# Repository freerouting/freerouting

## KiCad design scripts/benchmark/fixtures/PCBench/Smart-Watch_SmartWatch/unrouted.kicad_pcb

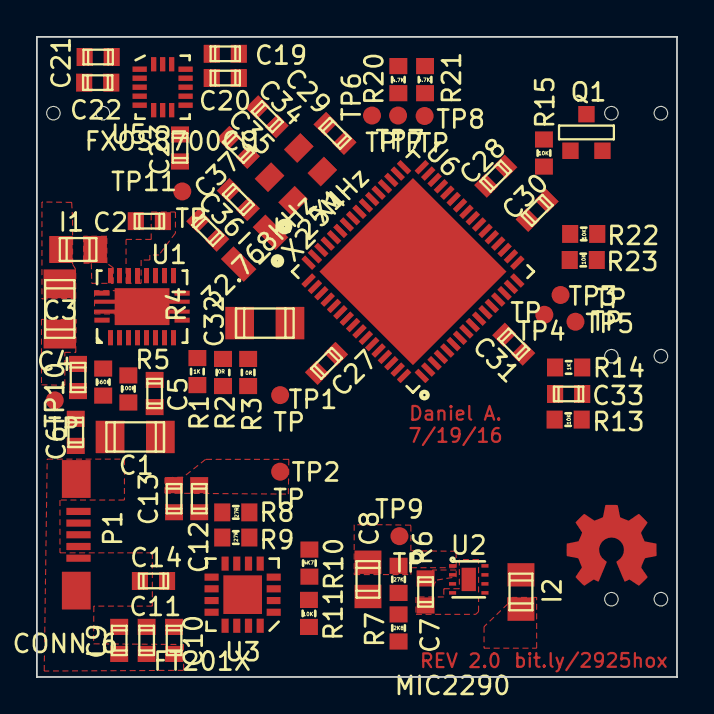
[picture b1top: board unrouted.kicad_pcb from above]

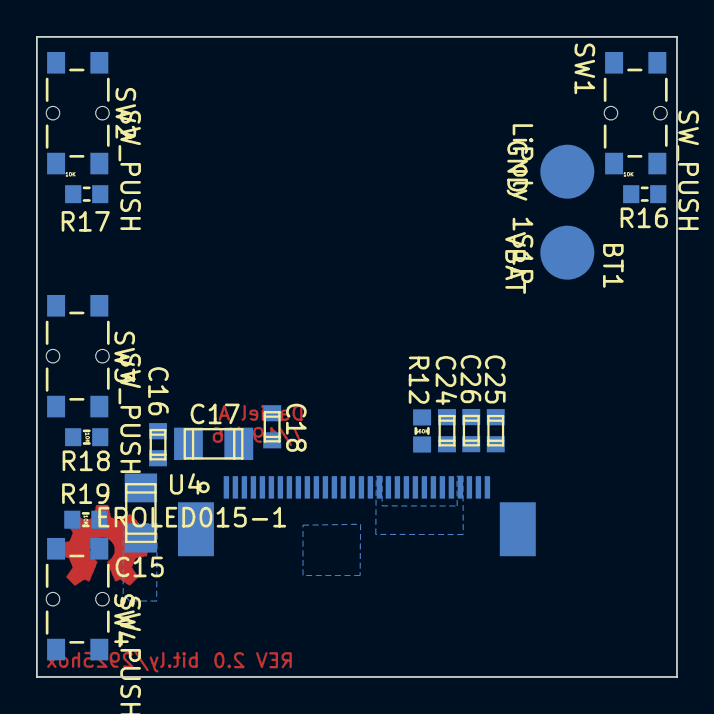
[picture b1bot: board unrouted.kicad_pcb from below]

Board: 4 copper layers, 35.6 x 35.6 mm, 88 parts (18 on the bottom side), 65 nets, no tracks yet.

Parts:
BT1: LiPoly 1S1P; CON_SM_3mm_2pin
C1, C3, C15, C32: 10u; c_1206
C2, C9, C19, C25: 4.7u; c_0603
C4: 27p; c_0603
C5: 180p; c_0603
C6, C10, C11, C14, C16, C20, C21, C22, C23, C26, C27, C28, C29, C30, C31, C33: 100n; c_0603
C7, C18, C24: 1u; c_0603
C8: 10u; c_0805
C12, C13: 47p; c_0603
C17: 4.7u; c_1206
C34, C35: 15p; c_0603
C36, C37: 9p1; c_0603
I1, I2: 10uH; r_0805
P1: CONN_6; USB-Micro-B
Q1: MMBT2222A; SOT23EBC
R1, R14: 1K; r_0603
R2, R3: 0R; r_0603
R4, R12: 560K; r_0603
R5: 100K; r_0603
R6: 27K; r_0603
R7: 2K8; r_0603
R8, R9: 27R; r_0603
R10: 4K7; r_0603
R11, R13, R15, R16, R17, R18, R19, R22, R23: 10K; r_0603
R20, R21: 4.7K; r_0603
SW1, SW2, SW3, SW4: SW_PUSH; 4.7x3.5mm_TCK_SW
TP1, TP2, TP3, TP4, TP5, TP6, TP7, TP8, TP9, TP10, TP11: TP; TP-1mm
U1: BQ25010; 20-VFQFN
U2: MIC2290; 8-VFDFN
U3: FT201X; QFN-16-ExPad
U4: EROLED015-1; ZIF_30pin_0.5pitch
U5: FXOS8700CQ; QFN-16
U6: PIC32MX370F512H; QFN-64
X1: 25MHz; ABM8
X2: 32.768KHz; Crystal_9HT10

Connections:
+3.3V: C3.1, C4.1, C7.1, C9.1, C10.1, C11.1, C18.1, C25.1, C26.1, C27.1, C28.1, C29.1, C30.1, C31.1, I1.2, I2.1, R4.2, R13.2, R20.1, R21.1, SW1.2, SW2.2, SW3.2, SW4.2, TP1.1, U2.2, U3.10, U4.4, U4.17, U4.18, U4.27, U6.10, U6.19, U6.26, U6.38, U6.57
+13V: C8.1, C15.1, C16.1, R6.1, TP9.1, U2.1, U4.2
/BAT/2: R22.2, R23.1, U6.17
/LCD/Sensors/CS: U4.19, U6.44
/LCD/Sensors/D0: U4.14, U6.60
/LCD/Sensors/D1: U4.13, U6.61
/LCD/Sensors/D2: U4.12, U6.62
/LCD/Sensors/D3: U4.11, U6.63
/LCD/Sensors/D4: U4.10, U6.64
/LCD/Sensors/D5: U4.9, U6.1
/LCD/Sensors/D6: U4.8, U6.2
/LCD/Sensors/D7: U4.7, U6.3
/LCD/Sensors/D/C: U4.20, U6.30
/LCD/Sensors/E: U4.15, U6.52
/LCD/Sensors/FX_RST: U5.16, U6.31
/LCD/Sensors/INT1: U5.11, U6.35
/LCD/Sensors/INT2: U5.9, U6.32
/LCD/Sensors/R/W: U4.16, U6.53
/LCD/Sensors/RES: U4.21, U6.43
/LCD/Sensors/SCL: R20.2, TP7.1, U3.16, U5.4, U6.37
/LCD/Sensors/SDA: R21.2, TP8.1, U3.2, U5.6, U6.36
/MOTOR: R15.2, U6.18
/RTCC: TP6.1, U6.42
/SW1: R16.2, SW1.1, U6.8
/SW2: R17.2, SW2.1, U6.6
/SW3: R18.2, SW3.1, U6.5
/SW4: R19.2, SW4.1, U6.4
/USB/Power/Boost-En: U2.3, U6.33
/USB/Power/CBUS2: U3.5, U6.24
/USB/Power/CBUS4: U3.4, U6.23
/USB/Power/D+: C13.1, P1.3, R9.1
/USB/Power/D-: C12.1, P1.2, R8.1
/USB/Power/FTDI_RST: U3.9, U6.29
/USB/Power/STAT1: U1.7, U6.59
/USB/Power/STAT2: U1.8, U6.58
/USB/Power/USB +5V: C1.1, C6.1, P1.1, R10.2, TP10.1, U1.6
/USB/Power/nPG: U1.14, U6.34
GND: BT1.2, C1.2, C2.2, C3.2, C5.2, C6.2, C7.2, C8.2, C9.2, C10.2, C11.2, C12.2, C13.2, C14.2, C15.2, C16.2, C17.2, C18.2, C19.2, C20.2, C21.2, C22.2, C23.2, C24.2, C25.2, C26.2, C27.2, C28.2, C29.2, C30.2, C31.2, C32.2, C33.2, C34.2, C35.2, C36.2, C37.2, P1.5, P1.6, Q1.1, R1.2, R2.2, R5.1, R7.2, R11.1, R12.1, R16.1, R17.1, R18.1, R19.1, R23.2, TP2.1, U1.3, U1.9, U1.15, U1.18, U1.20, U1.21, U2.4, U2.8, U2.9, U3.3, U3.13, U3.17, U4.1, U4.28, U4.30, U5.3, U5.5, U5.7, U5.10, U5.12, U5.13, U6.9, U6.20, U6.25, U6.41, U6.65, X1.3, X1.4
unnamed: C34.1, U6.39, X1.2
unnamed: C35.1, U6.40, X1.1
unnamed: TP3.1, U6.16
unnamed: TP4.1, U6.15
unnamed: C33.1, R13.1, R14.1
unnamed: C36.1, U6.48, X2.2
unnamed: C37.1, U6.47, X2.1
unnamed: Q1.2, R15.1
unnamed: R14.2, TP5.1, U6.7
unnamed: C32.1, U6.56
unnamed: I1.1, U1.19
unnamed: C4.2, C5.1, R4.1, R5.2, U1.2
unnamed: I2.2, U2.7
unnamed: R2.1, R3.2, U1.13
unnamed: R1.1, U1.12
unnamed: R10.1, R11.2, U3.15
unnamed: C14.1, U3.1, U3.8
unnamed: R9.2, U3.6
unnamed: R6.2, R7.1, U2.6
unnamed: R8.2, U3.7
unnamed: C19.1, C20.1, C21.1, U5.1, U5.14
unnamed: C22.1, U5.2
unnamed: C23.1, U5.8
unnamed: R12.2, U4.22
unnamed: C24.1, U4.26
unnamed: C17.1, U4.3
VBAT: BT1.1, C2.1, R3.1, R22.1, TP11.1, U1.4, U1.16, U1.17

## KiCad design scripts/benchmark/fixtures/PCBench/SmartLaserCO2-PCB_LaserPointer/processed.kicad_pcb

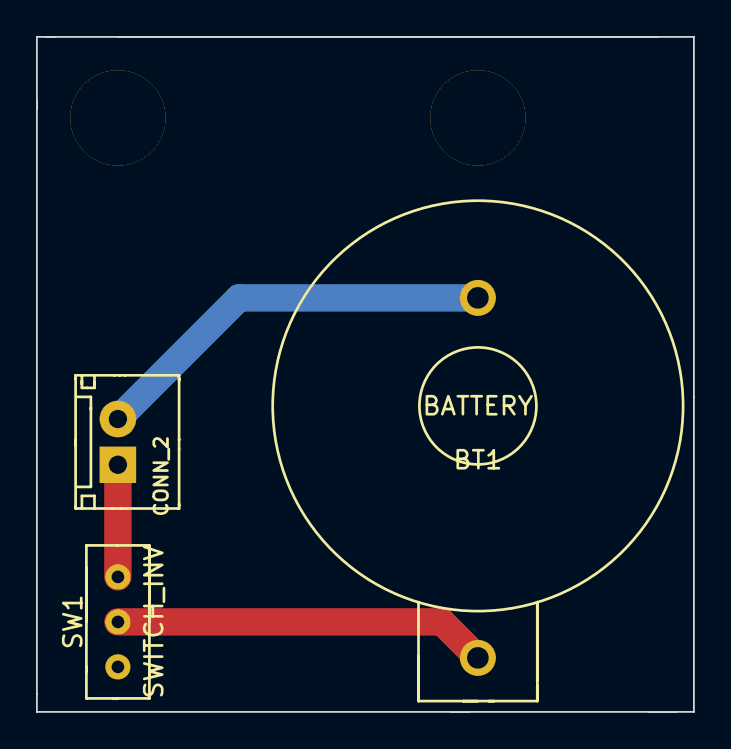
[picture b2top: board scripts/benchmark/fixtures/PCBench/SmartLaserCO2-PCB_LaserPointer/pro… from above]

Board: 2 copper layers, 36.5 x 37.5 mm, 5 parts (0 on the bottom side), 3 nets.

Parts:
BT1: BATTERY; CH25-2032LF
J1: CONN_2; PIN_ARRAY_2X1
Ref**: Val**; HOLE_M5
Ref**_2: Val**; HOLE_M5
SW1: SWITCH_INV; SS-12D00-G5

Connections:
GND: BT1.2, J1.2
unnamed: J1.1, SW1.1
unnamed: BT1.1, SW1.2

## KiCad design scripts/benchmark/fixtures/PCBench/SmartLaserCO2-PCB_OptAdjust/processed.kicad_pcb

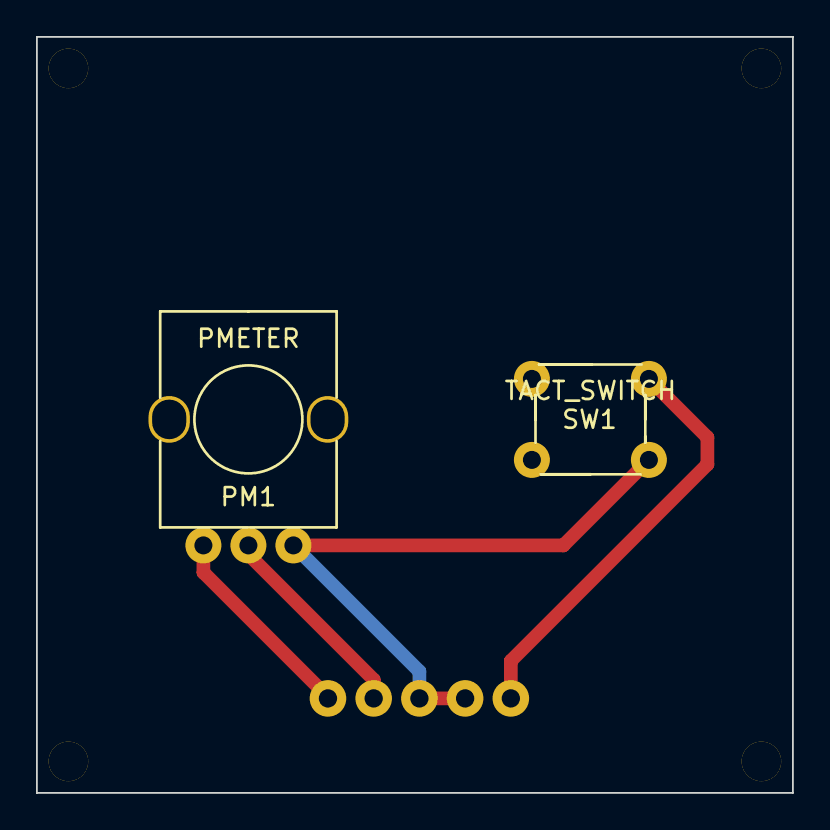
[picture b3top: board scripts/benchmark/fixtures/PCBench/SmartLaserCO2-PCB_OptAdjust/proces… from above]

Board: 2 copper layers, 42.0 x 42.0 mm, 7 parts (1 on the bottom side), 4 nets.

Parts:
J1: CONN_5; S5B-XH-A
PM1: PMETER; WH09A-2
Ref**: Val**; HOLE_M2
Ref**_2, Ref**_3, Ref**_4: Val**; HOLE_M2
SW1: TACT_SWITCH; TSA06131

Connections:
GND: J1.3, J1.4, PM1.3, SW1.2
unnamed: J1.1, PM1.1
unnamed: J1.2, PM1.2
unnamed: J1.5, SW1.1

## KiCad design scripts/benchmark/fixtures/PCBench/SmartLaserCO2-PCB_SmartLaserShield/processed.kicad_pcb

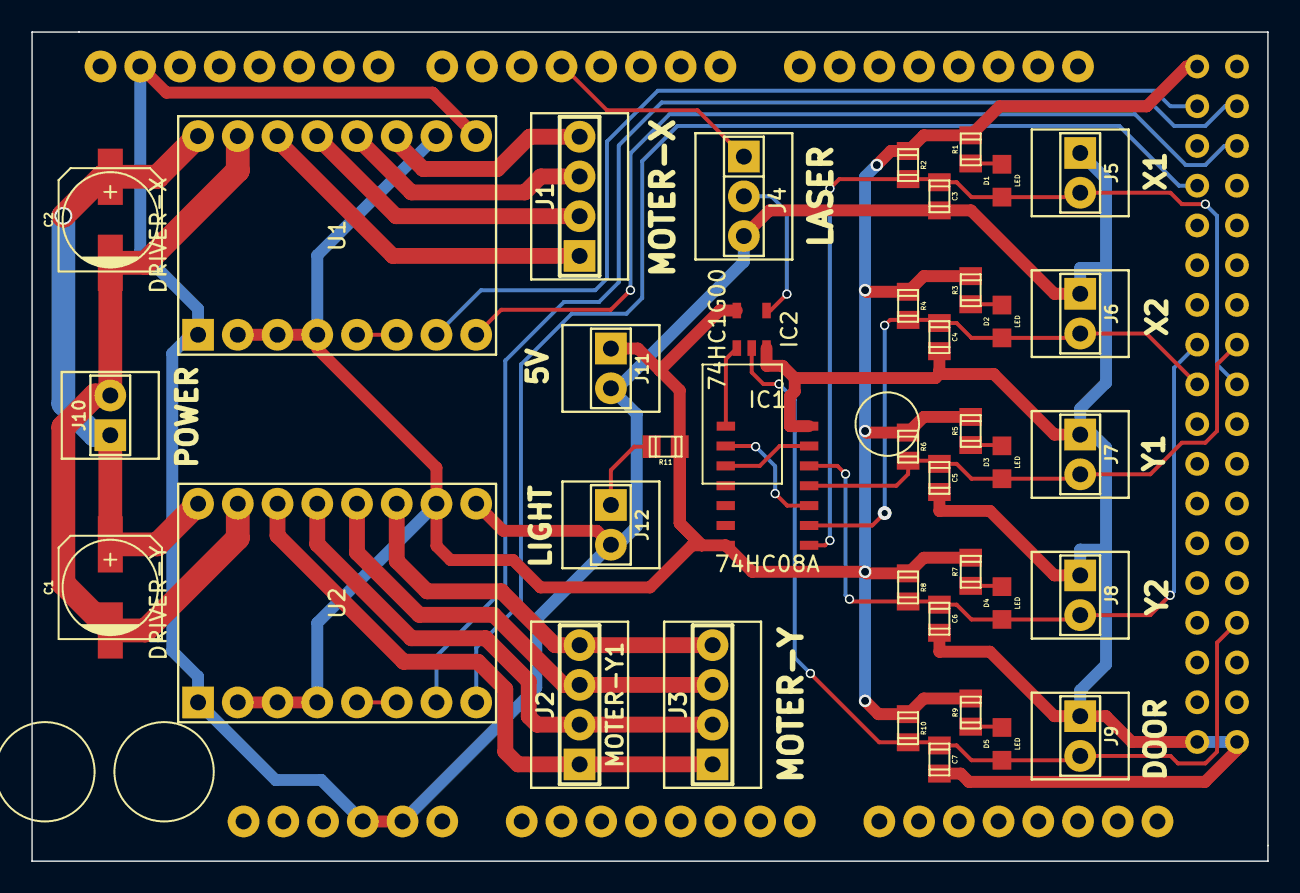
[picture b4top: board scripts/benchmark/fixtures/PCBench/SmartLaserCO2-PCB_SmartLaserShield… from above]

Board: 2 copper layers, 79.0 x 53.0 mm, 40 parts (0 on the bottom side), 34 nets.

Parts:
C1, C2: 100uF; C_ELEC_6.3x7.7
C3, C4, C5, C6, C7: 0u1; C_0805
D1, D2, D3, D4, D5: LED; C_LED
IC1: 74HC08A
IC2: 74HC1G00
J1: MOTER-X; PIN_ARRAY_4x1
J2: MOTER-Y1; PIN_ARRAY_4x1
J3: MOTER-Y; PIN_ARRAY_4x1
J4: LASER; PIN_ARRAY_3X1
J5: X1; PIN_ARRAY_2X1
J6: X2; PIN_ARRAY_2X1
J7: Y1; PIN_ARRAY_2X1
J8: Y2; PIN_ARRAY_2X1
J9: DOOR; PIN_ARRAY_2X1
J10: POWER; PIN_ARRAY_2X1
J11: 5V; PIN_ARRAY_2X1
J12: LIGHT; PIN_ARRAY_2X1
R1, R3, R5, R7, R9: 1K; C_0805
R2, R4, R6, R8, R10: 10K; C_0805
R11: 150; C_0805
U1: DRIVER-X; A4988
U2: DRIVER-Y; A4988
U3: ARDUINO_MEGA

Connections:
GND: C3.1, C4.1, C5.1, C6.1, C7.1, IC1.7, IC2.3, J4.3, J5.1, J6.1, J7.1, J8.1, J9.1, J11.2, J12.2, U1.1, U1.9, U2.1, U2.9, U3.GND1, U3.GND2, U3.GND3, U3.GND4, U3.GND5
unnamed: J1.2, U1.13
unnamed: J1.3, U1.12
unnamed: J1.4, U1.11
unnamed: J1.1, U1.14
unnamed: IC1.8, IC2.1
unnamed: J2.3, J3.3, U2.12
unnamed: J2.1, J3.1, U2.14
unnamed: J2.2, J3.2, U2.13
unnamed: J2.4, J3.4, U2.11
unnamed: U1.5, U1.6
unnamed: U2.5, U2.6
unnamed: IC1.3, IC1.9
unnamed: IC1.6, IC1.10
unnamed: J4.1, U3.4
unnamed: U1.7, U3.22
unnamed: U2.7, U3.23
unnamed: IC2.4, J4.2
unnamed: J12.1, R11.1
unnamed: U1.8, U3.25
unnamed: U2.8, U3.26
unnamed: D3.1, R5.2
unnamed: D1.1, R1.2
unnamed: C3.2, D1.2, IC1.1, J5.2, R2.1, U3.37
unnamed: D2.1, R3.2
unnamed: C4.2, D2.2, IC1.2, J6.2, R4.1, U3.36
unnamed: C6.2, D4.2, IC1.5, J8.2, R8.1, U3.34
unnamed: D5.1, R9.2
unnamed: C7.2, D5.2, IC2.2, J9.2, R10.1, U3.49
unnamed: C5.2, D3.2, IC1.4, J7.2, R6.1, U3.35
unnamed: D4.1, R7.2
unnamed: C1.1, C2.1, J10.1, U1.16, U2.16
unnamed: C1.2, C2.2, J10.2, U1.15, U2.15
VDD: IC1.14, IC2.5, J11.1, R1.1, R2.2, R3.1, R4.2, R5.1, R6.2, R7.1, R8.2, R9.1, R10.2, R11.2, U1.2, U1.3, U1.4, U1.10, U2.2, U2.3, U2.4, U2.10, U3.5V_4
